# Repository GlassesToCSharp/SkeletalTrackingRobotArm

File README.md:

# SkeletalTrackingRobotArm
**Objective**: Mimic user's arm motion with an Xbox Kinect V2

## Repository Contents
This repository should contain the code for the following:
1. C# code to read user's arm angles
2. Arduino code to communicate with the motors

## Hardware used
The following hardware was used:
1. Computer running Visual Studio (2015, but 2017 should be fine) and Microsoft Kinect SDK
2. Xbox Kinect **V2** (including adapter)
3. Arduino/Genuino UNO
4. Dynamixel RX-28 servo motors (x6)
5. Custom RS485 Comms board
6. Assorted cables/wires
7. A 3D-printed body (optional)

## Simplified code break-down
The code is split as follows:
### C# (Visual Studio)
The purpose of the C# code was to handle the harder and more computationally intensive algorithms. It is also required to talk to the Kinect and send the arm angles to the Arduino.

The code uses the vectors from various skeletal points. Joint angles are calculated using vector angles from joint-to-joint. The angles are then sent to the Arduino using standard serial protocol.

### Arduino
The Arduino is simply used to talk to the motors. There is no special algorithm going on, just serial data sent to the motors via the custom RS485 comms board.

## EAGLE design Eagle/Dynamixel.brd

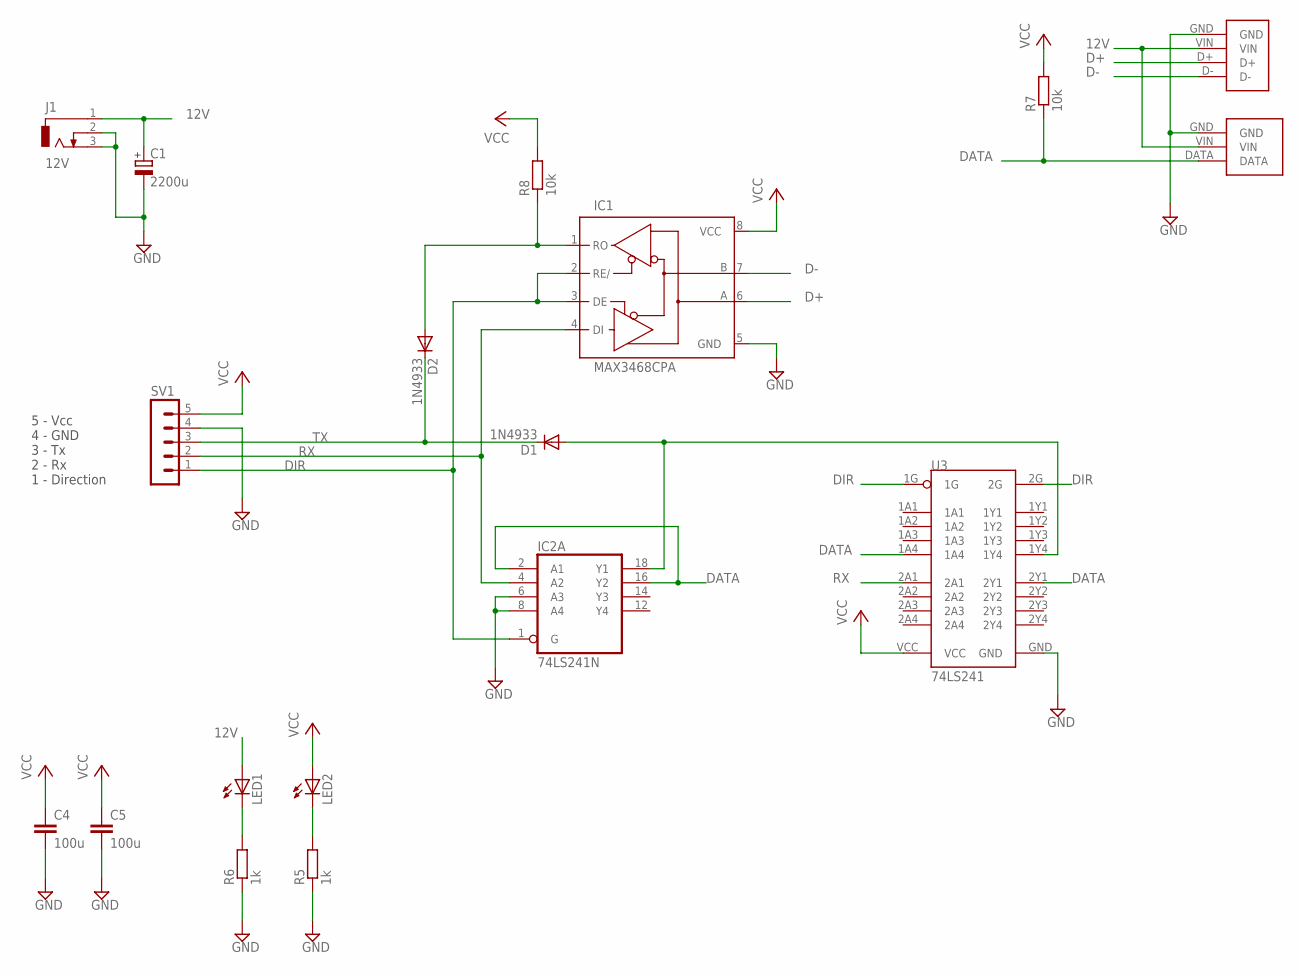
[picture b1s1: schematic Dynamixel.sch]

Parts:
C1: 2200u; E5-13
C4, C5: 100u; C0805
D1, D2: 1N4933; DO41-10
IC1: MAX3468CPA; DIL08
IC2: 74LS241N; DIL20
J1: 12V; DCJ0303
LED1, LED2: LED_ELD260; LED_LD260
R5, R6: 1k; R0805
R7, R8: 10k; R0805
SV1: MA05-1
U3: 74LS241-N
U$1: DYN-RA-3
U$2: DYN-RA-4

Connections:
12V: C1.+, J1.1, LED1.A, U$1.VIN, U$2.VIN
D+: IC1.6 (A), U$2.D+
D-: IC1.7 (B), U$2.D-
DATA: IC2.2 (A1), IC2.16 (Y2), R7.1, U3.1A4, U3.2Y1, U$1.DATA
DIR: IC1.2 (RE/), IC1.3 (DE), IC2.1 (G), SV1.1, U3.1G, U3.2G
GND: C1.-, C4.2, C5.2, IC1.5 (GND), IC2.6 (A3), IC2.8 (A4), IC2.10 (GND), J1.2, J1.3, R5.1, R6.1, SV1.4, U3.GND, U$1.GND, U$2.GND
unnamed: D2.A, IC1.1 (RO), R8.1
unnamed: D1.A, IC2.18 (Y1), U3.1Y4
unnamed: LED1.K (C), R6.2
unnamed: LED2.K (C), R5.2
RX: IC1.4 (DI), IC2.4 (A2), SV1.2, U3.2A1
TX: D1.C, D2.C, SV1.3
VCC: C4.1, C5.1, IC1.8 (VCC), IC2.20 (VCC), LED2.A, R7.2, R8.2, SV1.5, U3.VCC

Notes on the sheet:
5 - Vcc 4 - GND 3 - Tx 2 - Rx 1 - Direction

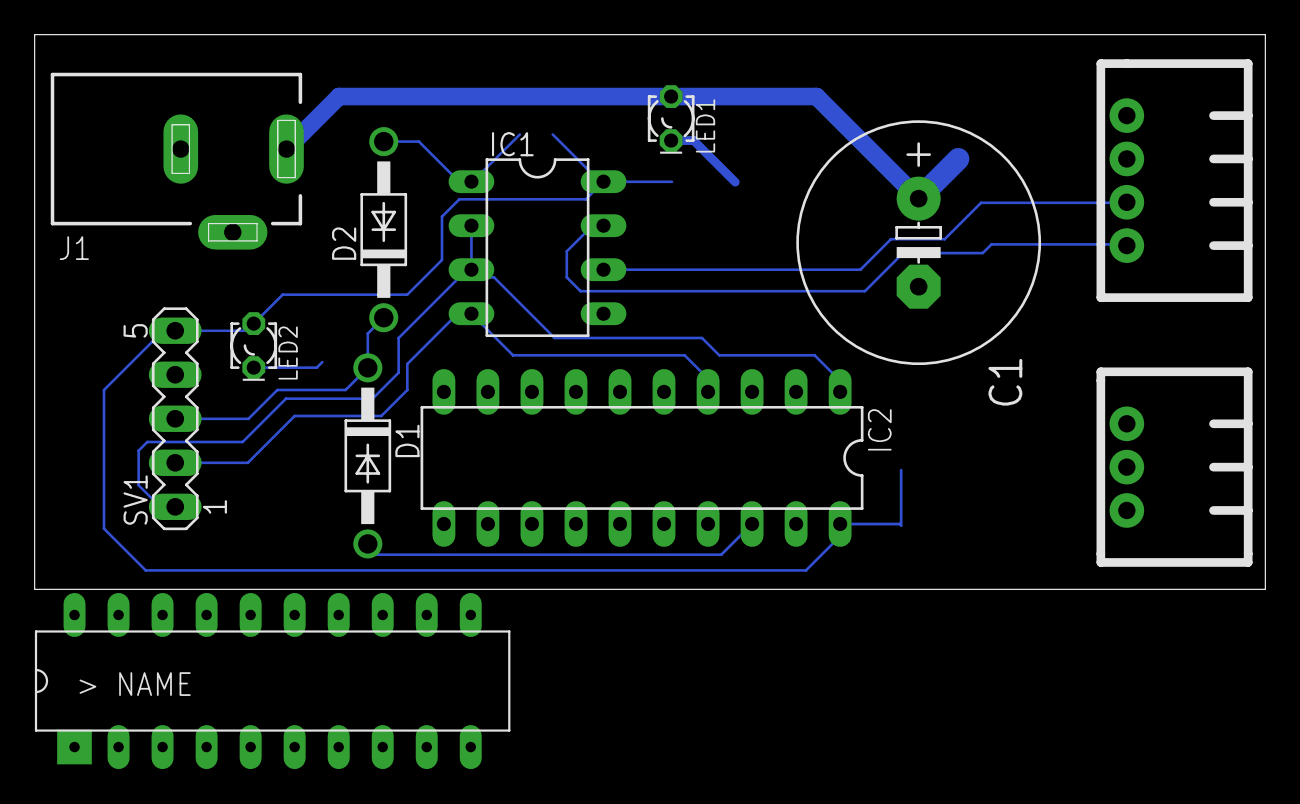
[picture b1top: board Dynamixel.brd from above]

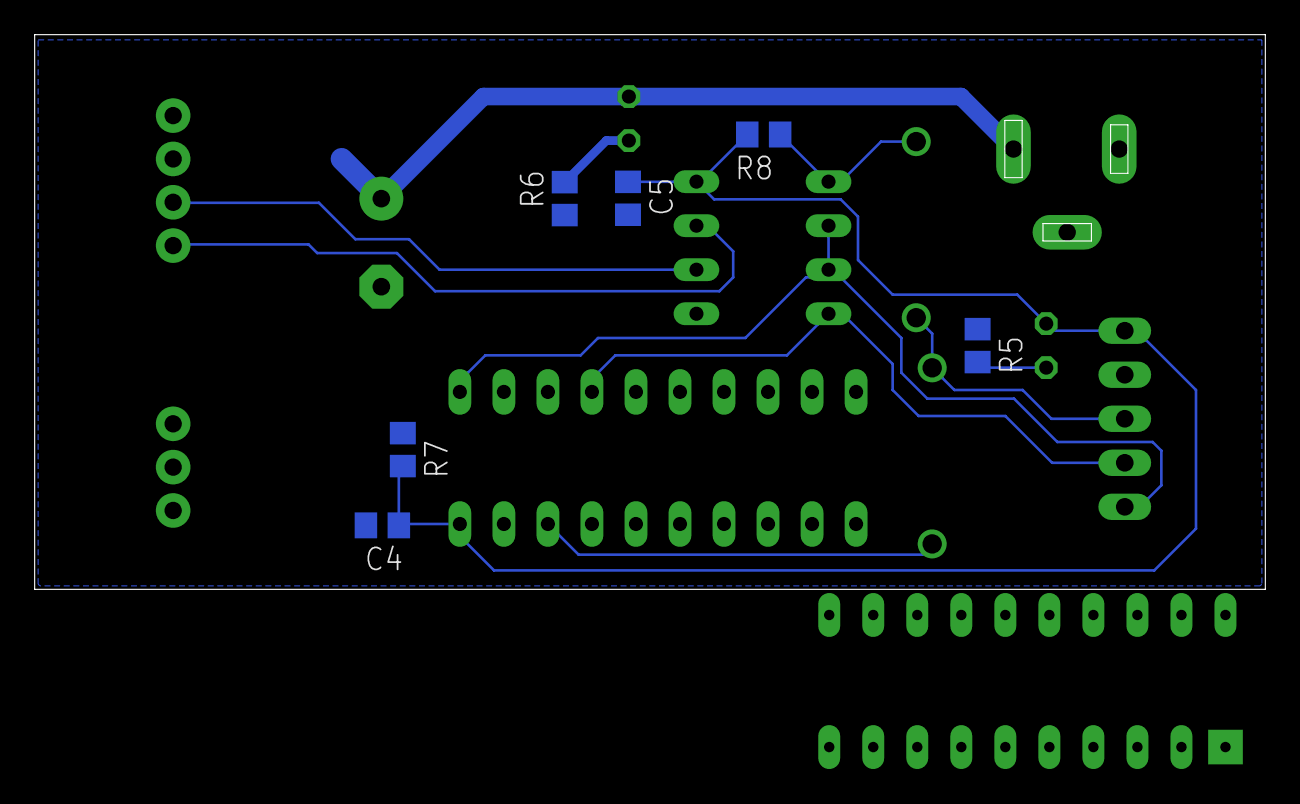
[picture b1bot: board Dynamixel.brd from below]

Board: 2 copper layers, 71.0 x 32.0 mm, 18 parts (6 on the bottom side), 13 nets.

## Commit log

2018-10-28 Updated ReadMe
    Added additional detail to the ReadMe file, which should help understanding what is required to get the full thing working.
2018-10-29 Initial commit.
    Initial commit for both VS code and Arduino code.
2018-11-03 Created separate files fo serial and vector classes, and added ability to select skeleton to follow.
    Changes:
    ClassVector3
    - Separate file for Vector3 and Plane classes.
    LibrarySerialInterface
    - Separate interface for serial communications.
    - Uses Singleton design, as only one instace can exist.
2018-11-10 Implemented Shoulder roll to the Kinect algorithms and the Arduino code.
    Changes:
    Constants
    - Increased the maximum value of the motor to 600.
    DynamixelMotorControl
    - Created function to set the motor position.
    RobotArm
2020-10-31 Rebuilt arm with better natural values, and removed SoftSerial
    SoftSerial seemed to be failing. Time to use the hardware serial, but for two-baud communications. Lets see if this works!
2020-11-07 Improved communications with motors
    Implemented code for Arduino Mega (uses two hardware serial peripherals).
    Implemented 2-way communication so that the arm requests data from tracker.
2020-11-07 Added moving average filter to angle values
2020-11-21 Temproarily added motor speed determination
    Thia doesn't seem to work well, but I'm adding this is so that it is tracked and there is a record of it. Who knows, I might come back to this in the future.
2020-11-21 Removed commented out code
2020-11-21 Removed unused/unnecessary code
2020-11-21 Added some dampening to the motors
    Arbitraty number is a guess. No actul calculation was done. Number might be from 0 to 255, or it might be the angle in degrees. No idea.
2020-11-22 Send data at specific frequency
    The data being sent should be done by the host machine, not the receiving end. Test showed that around 60ms is the fastest time between data transmissions. A nice 100ms is OCD-friendly and prevents a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
2020-11-22 Addressed some warnings
2021-02-07 Formatting
2021-02-21 Tidying update
2021-02-21 Set up layout for displaying a projected skeletal track
2021-02-22 Created a Matrix class to handle complex calculations
2021-02-22 Removed unnecessary statements in Matrix
2021-02-23 Simplified the Matrix class by removing a lot of duplicate code
2021-02-23 Created a new Matrix constructor to set custom values on initialising
2021-02-23 Formatted Matrix class
2021-02-24 Restructured ClassVector3
2021-02-24 Restructured and applied operators to Matrix class
2021-02-24 Removed one-indexing for matrices
2021-02-25 Applied zero-indexing to operations
2021-02-27 Added forward kinematics to get projected position of the right arm
    Started using Canvas to draw the arm, but this proved to be a lot more finicky to play with. Reverted to using another ViewBox with the projected image. This worked better because the coordinates use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
2021-03-02 Added basic unit tests for Matrix
2021-03-06 Added tests for Vector3
2021-03-06 Removed redundant method
2021-03-07 Improved Vector3 constructor and equality, and added testing
2021-03-07 Tidied up display and a bit of code
2021-03-07 Created Kinematics class with tests
    This contains the calculations required to determine forward and reverse kinematics for arms joints.
2021-03-09 Created and implemented Point3 class
2021-03-10 Added NaN check and actually used Point3 instead of Vector3 where required
2021-03-11 Created a Plane class
2021-03-11 Privatised setting properties for Point3, Vector3, and Plane classes
2021-03-11 Updated shoulder roll equation
    Uses planes instead of vectors
2021-03-11 Updated Kinematics test variables and values
2021-03-11 Added a perpendicularity compensator
2021-03-14 Use points to determine shoulder angles
    Trying out using points instead of vectors, but I think vectors are the way forward.
2021-03-14 Reverted to using vectors
    Using points is bluelocks and overcomplicated.
2021-03-14 Removed negativity on shoulder yaw
    It didn't feel right, and now that it is removed, the angles work better. Added additional tests to prove this.
2021-03-14 Refactored and improved calculating shoulder roll
2021-03-14 Reverted to passing vectors to methods instead of points
    It means fewer duplicate vector creations (unnecessary code running multiple times).
2021-03-16 Addressed kinematics to better fit tests
2021-03-17 Fixed incorrect D assignment for Plane
2021-03-17 Added additional option (and test) for dot product
2021-03-17 Created a set of tests testing the inverse and forward kinematics
2021-03-17 Updated points to match across tests
2021-03-17 Separated forward/inverse kinematics into separate files
2021-03-17 Added/updated comments
2021-03-17 Applied all previous modifications to main code
    It only bloody works!
2021-03-20 Updated UI to show headers over skeletons
2021-03-20 Updated comments, and tidied up code.
    Removed unused variables, and updated old comments.
2021-03-23 Added maths and tests for moving left arm
2021-03-23 Implemented forward and inverse kinematics to UI and sensor data
2021-03-25 Updated constants and constant implementations
2021-03-25 Addressed pointer issue
2021-03-31 Added schematics to version control
2021-03-31 Removed incorrect TTL comms configuration, and grouped comms chips designs
2021-03-31 Replaced diodes with AND gate
2021-04-01 Switched Vcc and GND on the connector, and grouped components
2021-04-24 Improved right shoulder roll kinematics
2021-04-24 Improved left shoulder roll kinematics
2021-04-24 Added display of left arm angles
2021-04-24 Added method to test motor communications
    Involves no kinematics. Just motor control.
2021-04-24 Start/stop motion by opening/closing both hands
2021-04-24 Improved servo control
2021-04-24 Converted Func to local function
2021-04-24 Removed ComboBox of bodies to choose from
    It was getting difficult to track who could use the program and who couldn't. If a new user wanted to use it, you'd have to close and re-open. Will implement a single body tracker at some point.
2021-04-25 Updated Plane calculations
2021-04-25 Fixed bug in test
2021-04-25 Added a try/catch when writing to the serial
    Just in case the connection terminates without closing (sudden unplug).
2021-04-25 Use vector (point difference) instead of point, when calculating the distance from plane
    The Dot product messes up otherwise.
2021-04-25 Added custom functions to set the range of motors
    The library functions don't work as well. They come up with errors. So, I created custom functions that actually do hat they're supposed to do, according to the Dynamixel Protocol 1.0.
2021-05-02 Increased font size of canvas headers
    Also decreased font size of angles
2021-05-02 Send data to motors
